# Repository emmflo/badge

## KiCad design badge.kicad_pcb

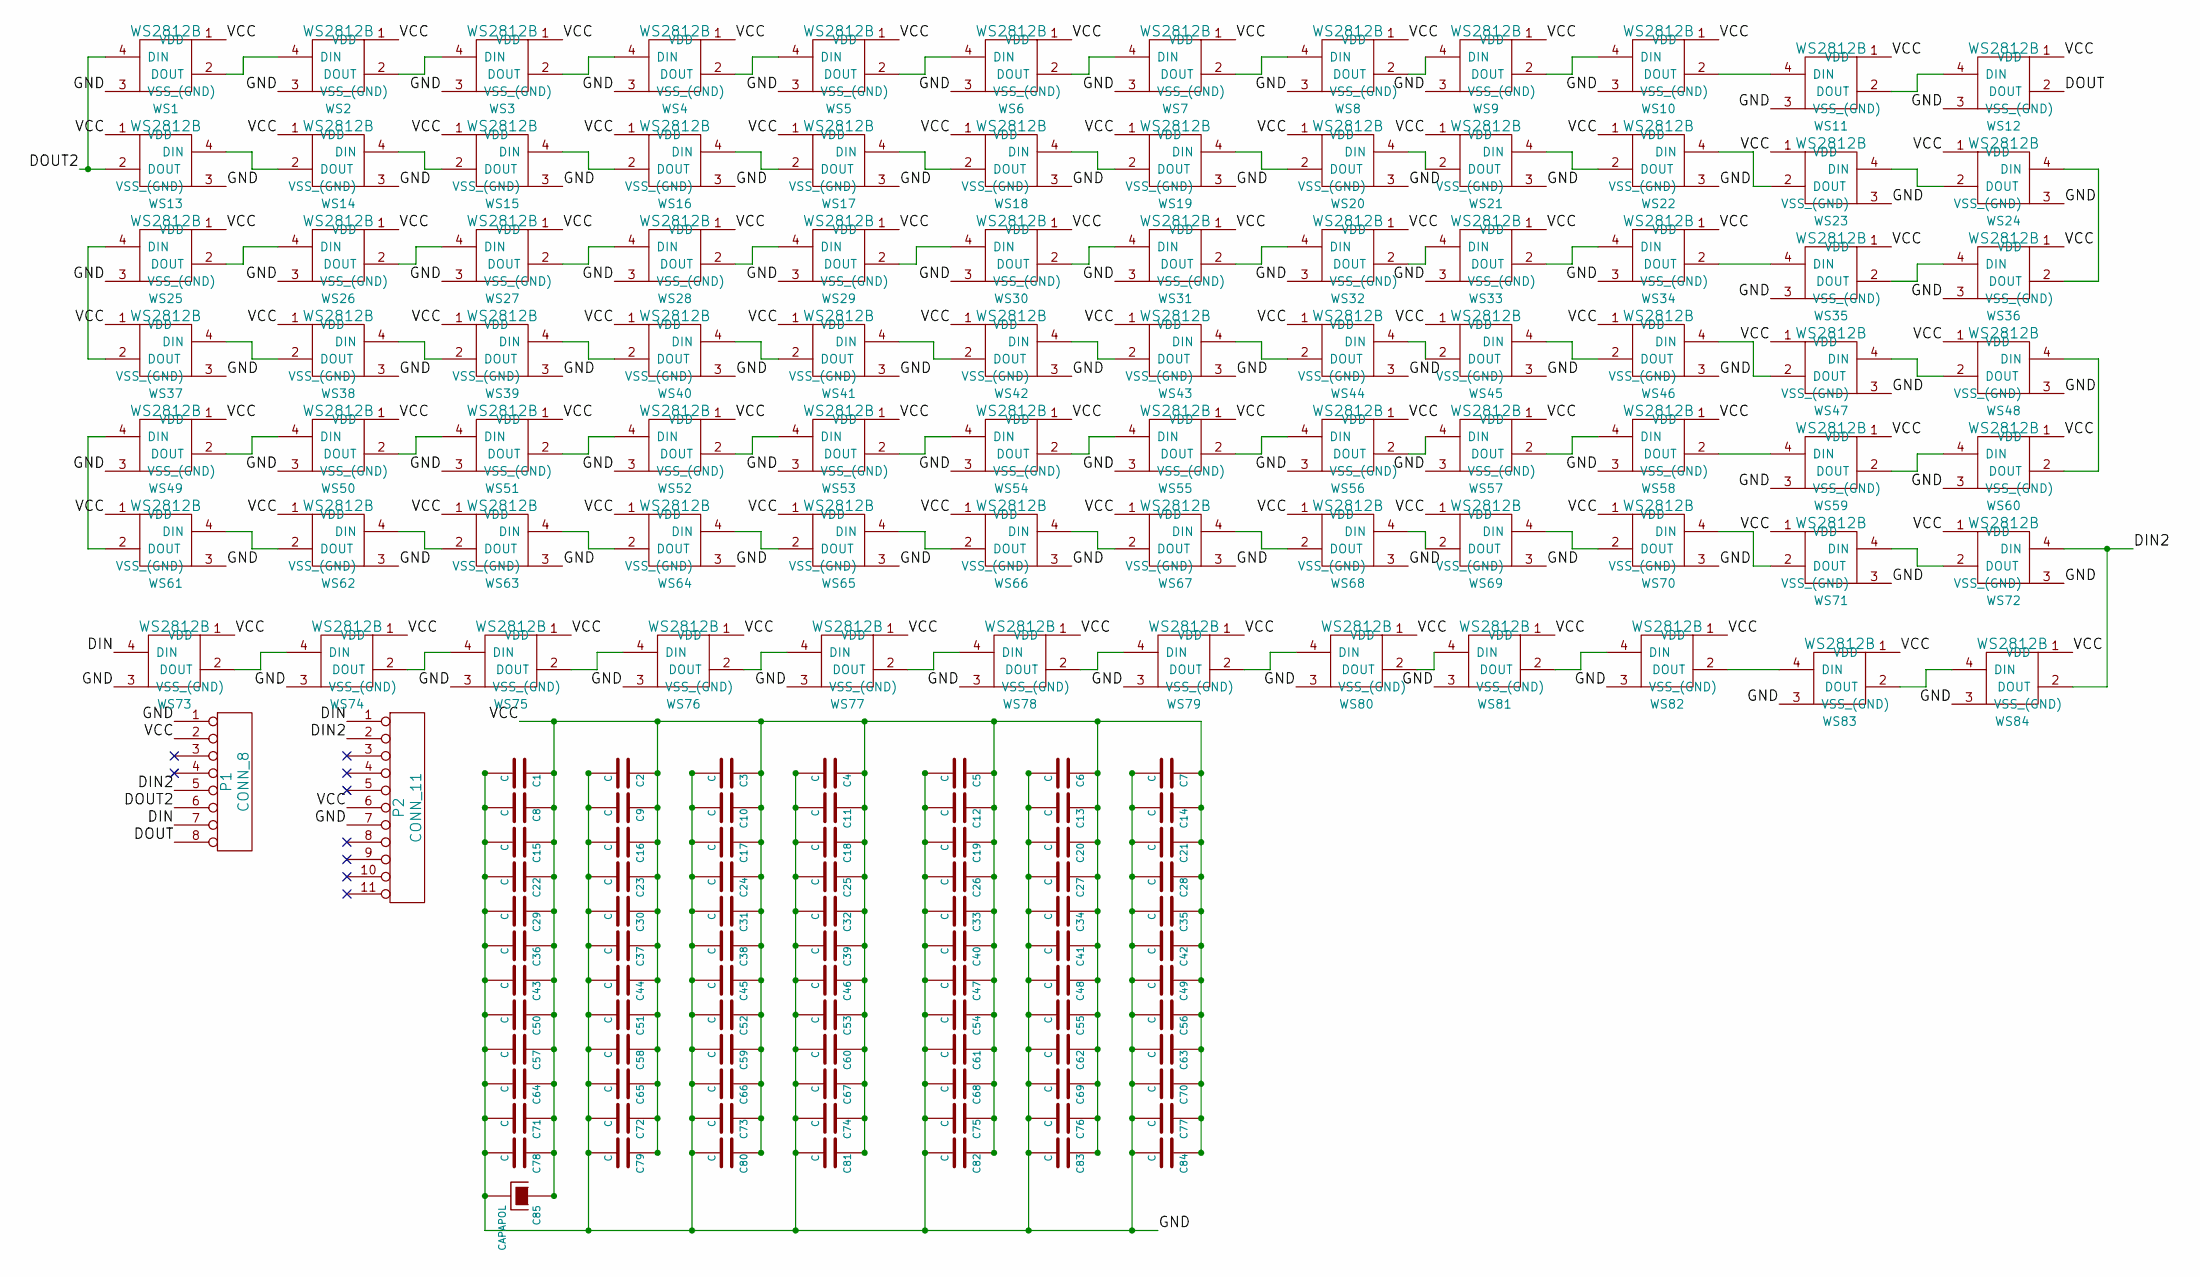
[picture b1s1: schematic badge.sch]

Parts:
C1, C2, C3, C4, C5, C6, C7, C8, C9, C10, C11, C12, C13, C14, C15, C16, C17, C18, C19, C20, C21, C22, C23, C24, C25, C26, C27, C28, C29, C30, C31, C32, C33, C34, C35, C36, C37, C38, C39, C40, C41, C42, C43, C44, C45, C46, C47, C48, C49, C50, C51, C52, C53, C54, C55, C56, C57, C58, C59, C60, C61, C62, C63, C64, C65, C66, C67, C68, C69, C70, C71, C72, C73, C74, C75, C76, C77, C78, C79, C80, C81, C82, C83, C84: C; C_0805_HandSoldering
C85: CAPAPOL
P1: CONN_8; Pin_Header_Straight_1x08
P2: CONN_11
WS1, WS2, WS3, WS4, WS5, WS6, WS7, WS8, WS9, WS10, WS11, WS12, WS13, WS14, WS15, WS16, WS17, WS18, WS19, WS20, WS21, WS22, WS23, WS24, WS25, WS26, WS27, WS28, WS29, WS30, WS31, WS32, WS33, WS34, WS35, WS36, WS37, WS38, WS39, WS40, WS41, WS42, WS43, WS44, WS45, WS46, WS47, WS48, WS49, WS50, WS51, WS52, WS53, WS54, WS55, WS56, WS57, WS58, WS59, WS60, WS61, WS62, WS63, WS64, WS65, WS66, WS67, WS68, WS69, WS70, WS71, WS72, WS73, WS74, WS75, WS76, WS77, WS78, WS79, WS80, WS81, WS82, WS83, WS84: WS2812B

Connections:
/DIN: P1.7, P2.1, WS73.4 (DIN)
/DIN2: P1.5, P2.2, WS72.4 (DIN), WS84.2 (DOUT)
/DOUT: P1.8, WS12.2 (DOUT)
/DOUT2: P1.6, WS1.4 (DIN), WS13.2 (DOUT)
/GND: C1.2, C2.2, C3.2, C4.2, C5.2, C6.2, C7.2, C8.2, C9.2, C10.2, C11.2, C12.2, C13.2, C14.2, C15.2, C16.2, C17.2, C18.2, C19.2, C20.2, C21.2, C22.2, C23.2, C24.2, C25.2, C26.2, C27.2, C28.2, C29.2, C30.2, C31.2, C32.2, C33.2, C34.2, C35.2, C36.2, C37.2, C38.2, C39.2, C40.2, C41.2, C42.2, C43.2, C44.2, C45.2, C46.2, C47.2, C48.2, C49.2, C50.2, C51.2, C52.2, C53.2, C54.2, C55.2, C56.2, C57.2, C58.2, C59.2, C60.2, C61.2, C62.2, C63.2, C64.2, C65.2, C66.2, C67.2, C68.2, C69.2, C70.2, C71.2, C72.2, C73.2, C74.2, C75.2, C76.2, C77.2, C78.2, C79.2, C80.2, C81.2, C82.2, C83.2, C84.2, C85.2, P1.1, P2.7, WS1.3 (VSS_(GND)), WS2.3 (VSS_(GND)), WS3.3 (VSS_(GND)), WS4.3 (VSS_(GND)), WS5.3 (VSS_(GND)), WS6.3 (VSS_(GND)), WS7.3 (VSS_(GND)), WS8.3 (VSS_(GND)), WS9.3 (VSS_(GND)), WS10.3 (VSS_(GND)), WS11.3 (VSS_(GND)), WS12.3 (VSS_(GND)), WS13.3 (VSS_(GND)), WS14.3 (VSS_(GND)), WS15.3 (VSS_(GND)), WS16.3 (VSS_(GND)), WS17.3 (VSS_(GND)), WS18.3 (VSS_(GND)), WS19.3 (VSS_(GND)), WS20.3 (VSS_(GND)), WS21.3 (VSS_(GND)), WS22.3 (VSS_(GND)), WS23.3 (VSS_(GND)), WS24.3 (VSS_(GND)), WS25.3 (VSS_(GND)), WS26.3 (VSS_(GND)), WS27.3 (VSS_(GND)), WS28.3 (VSS_(GND)), WS29.3 (VSS_(GND)), WS30.3 (VSS_(GND)), WS31.3 (VSS_(GND)), WS32.3 (VSS_(GND)), WS33.3 (VSS_(GND)), WS34.3 (VSS_(GND)), WS35.3 (VSS_(GND)), WS36.3 (VSS_(GND)), WS37.3 (VSS_(GND)), WS38.3 (VSS_(GND)), WS39.3 (VSS_(GND)), WS40.3 (VSS_(GND)), WS41.3 (VSS_(GND)), WS42.3 (VSS_(GND)), WS43.3 (VSS_(GND)), WS44.3 (VSS_(GND)), WS45.3 (VSS_(GND)), WS46.3 (VSS_(GND)), WS47.3 (VSS_(GND)), WS48.3 (VSS_(GND)), WS49.3 (VSS_(GND)), WS50.3 (VSS_(GND)), WS51.3 (VSS_(GND)), WS52.3 (VSS_(GND)), WS53.3 (VSS_(GND)), WS54.3 (VSS_(GND)), WS55.3 (VSS_(GND)), WS56.3 (VSS_(GND)), WS57.3 (VSS_(GND)), WS58.3 (VSS_(GND)), WS59.3 (VSS_(GND)), WS60.3 (VSS_(GND)), WS61.3 (VSS_(GND)), WS62.3 (VSS_(GND)), WS63.3 (VSS_(GND)), WS64.3 (VSS_(GND)), WS65.3 (VSS_(GND)), WS66.3 (VSS_(GND)), WS67.3 (VSS_(GND)), WS68.3 (VSS_(GND)), WS69.3 (VSS_(GND)), WS70.3 (VSS_(GND)), WS71.3 (VSS_(GND)), WS72.3 (VSS_(GND)), WS73.3 (VSS_(GND)), WS74.3 (VSS_(GND)), WS75.3 (VSS_(GND)), WS76.3 (VSS_(GND)), WS77.3 (VSS_(GND)), WS78.3 (VSS_(GND)), WS79.3 (VSS_(GND)), WS80.3 (VSS_(GND)), WS81.3 (VSS_(GND)), WS82.3 (VSS_(GND)), WS83.3 (VSS_(GND)), WS84.3 (VSS_(GND))
/VCC: C1.1, C2.1, C3.1, C4.1, C5.1, C6.1, C7.1, C8.1, C9.1, C10.1, C11.1, C12.1, C13.1, C14.1, C15.1, C16.1, C17.1, C18.1, C19.1, C20.1, C21.1, C22.1, C23.1, C24.1, C25.1, C26.1, C27.1, C28.1, C29.1, C30.1, C31.1, C32.1, C33.1, C34.1, C35.1, C36.1, C37.1, C38.1, C39.1, C40.1, C41.1, C42.1, C43.1, C44.1, C45.1, C46.1, C47.1, C48.1, C49.1, C50.1, C51.1, C52.1, C53.1, C54.1, C55.1, C56.1, C57.1, C58.1, C59.1, C60.1, C61.1, C62.1, C63.1, C64.1, C65.1, C66.1, C67.1, C68.1, C69.1, C70.1, C71.1, C72.1, C73.1, C74.1, C75.1, C76.1, C77.1, C78.1, C79.1, C80.1, C81.1, C82.1, C83.1, C84.1, C85.1, P1.2, P2.6, WS1.1 (VDD), WS2.1 (VDD), WS3.1 (VDD), WS4.1 (VDD), WS5.1 (VDD), WS6.1 (VDD), WS7.1 (VDD), WS8.1 (VDD), WS9.1 (VDD), WS10.1 (VDD), WS11.1 (VDD), WS12.1 (VDD), WS13.1 (VDD), WS14.1 (VDD), WS15.1 (VDD), WS16.1 (VDD), WS17.1 (VDD), WS18.1 (VDD), WS19.1 (VDD), WS20.1 (VDD), WS21.1 (VDD), WS22.1 (VDD), WS23.1 (VDD), WS24.1 (VDD), WS25.1 (VDD), WS26.1 (VDD), WS27.1 (VDD), WS28.1 (VDD), WS29.1 (VDD), WS30.1 (VDD), WS31.1 (VDD), WS32.1 (VDD), WS33.1 (VDD), WS34.1 (VDD), WS35.1 (VDD), WS36.1 (VDD), WS37.1 (VDD), WS38.1 (VDD), WS39.1 (VDD), WS40.1 (VDD), WS41.1 (VDD), WS42.1 (VDD), WS43.1 (VDD), WS44.1 (VDD), WS45.1 (VDD), WS46.1 (VDD), WS47.1 (VDD), WS48.1 (VDD), WS49.1 (VDD), WS50.1 (VDD), WS51.1 (VDD), WS52.1 (VDD), WS53.1 (VDD), WS54.1 (VDD), WS55.1 (VDD), WS56.1 (VDD), WS57.1 (VDD), WS58.1 (VDD), WS59.1 (VDD), WS60.1 (VDD), WS61.1 (VDD), WS62.1 (VDD), WS63.1 (VDD), WS64.1 (VDD), WS65.1 (VDD), WS66.1 (VDD), WS67.1 (VDD), WS68.1 (VDD), WS69.1 (VDD), WS70.1 (VDD), WS71.1 (VDD), WS72.1 (VDD), WS73.1 (VDD), WS74.1 (VDD), WS75.1 (VDD), WS76.1 (VDD), WS77.1 (VDD), WS78.1 (VDD), WS79.1 (VDD), WS80.1 (VDD), WS81.1 (VDD), WS82.1 (VDD), WS83.1 (VDD), WS84.1 (VDD)
unnamed: WS1.2 (DOUT), WS2.4 (DIN)
unnamed: WS2.2 (DOUT), WS3.4 (DIN)
unnamed: WS3.2 (DOUT), WS4.4 (DIN)
unnamed: WS4.2 (DOUT), WS5.4 (DIN)
unnamed: WS5.2 (DOUT), WS6.4 (DIN)
unnamed: WS6.2 (DOUT), WS7.4 (DIN)
unnamed: WS7.2 (DOUT), WS8.4 (DIN)
unnamed: WS8.2 (DOUT), WS9.4 (DIN)
unnamed: WS10.2 (DOUT), WS11.4 (DIN)
unnamed: WS9.2 (DOUT), WS10.4 (DIN)
unnamed: WS11.2 (DOUT), WS12.4 (DIN)
unnamed: WS13.4 (DIN), WS14.2 (DOUT)
unnamed: WS14.4 (DIN), WS15.2 (DOUT)
unnamed: WS15.4 (DIN), WS16.2 (DOUT)
unnamed: WS16.4 (DIN), WS17.2 (DOUT)
unnamed: WS17.4 (DIN), WS18.2 (DOUT)
unnamed: WS18.4 (DIN), WS19.2 (DOUT)
unnamed: WS19.4 (DIN), WS20.2 (DOUT)
unnamed: WS20.4 (DIN), WS21.2 (DOUT)
unnamed: WS21.4 (DIN), WS22.2 (DOUT)
unnamed: WS22.4 (DIN), WS23.2 (DOUT)
unnamed: WS23.4 (DIN), WS24.2 (DOUT)
unnamed: WS24.4 (DIN), WS36.2 (DOUT)
unnamed: WS25.2 (DOUT), WS26.4 (DIN)
unnamed: WS25.4 (DIN), WS37.2 (DOUT)
unnamed: WS26.2 (DOUT), WS27.4 (DIN)
unnamed: WS27.2 (DOUT), WS28.4 (DIN)
unnamed: WS28.2 (DOUT), WS29.4 (DIN)
unnamed: WS29.2 (DOUT), WS30.4 (DIN)
unnamed: WS30.2 (DOUT), WS31.4 (DIN)
unnamed: WS31.2 (DOUT), WS32.4 (DIN)
unnamed: WS32.2 (DOUT), WS33.4 (DIN)
unnamed: WS33.2 (DOUT), WS34.4 (DIN)
unnamed: WS34.2 (DOUT), WS35.4 (DIN)
unnamed: WS35.2 (DOUT), WS36.4 (DIN)
unnamed: WS37.4 (DIN), WS38.2 (DOUT)
unnamed: WS38.4 (DIN), WS39.2 (DOUT)
unnamed: WS39.4 (DIN), WS40.2 (DOUT)
unnamed: WS40.4 (DIN), WS41.2 (DOUT)
unnamed: WS41.4 (DIN), WS42.2 (DOUT)
unnamed: WS42.4 (DIN), WS43.2 (DOUT)
unnamed: WS43.4 (DIN), WS44.2 (DOUT)
unnamed: WS44.4 (DIN), WS45.2 (DOUT)
unnamed: WS45.4 (DIN), WS46.2 (DOUT)
unnamed: WS46.4 (DIN), WS47.2 (DOUT)
unnamed: WS47.4 (DIN), WS48.2 (DOUT)
unnamed: WS48.4 (DIN), WS60.2 (DOUT)
unnamed: WS49.2 (DOUT), WS50.4 (DIN)
unnamed: WS49.4 (DIN), WS61.2 (DOUT)
unnamed: WS50.2 (DOUT), WS51.4 (DIN)
unnamed: WS51.2 (DOUT), WS52.4 (DIN)
unnamed: WS52.2 (DOUT), WS53.4 (DIN)
unnamed: WS53.2 (DOUT), WS54.4 (DIN)
unnamed: WS54.2 (DOUT), WS55.4 (DIN)
unnamed: WS55.2 (DOUT), WS56.4 (DIN)
unnamed: WS56.2 (DOUT), WS57.4 (DIN)
unnamed: WS57.2 (DOUT), WS58.4 (DIN)
unnamed: WS58.2 (DOUT), WS59.4 (DIN)
unnamed: WS59.2 (DOUT), WS60.4 (DIN)
unnamed: WS61.4 (DIN), WS62.2 (DOUT)
unnamed: WS62.4 (DIN), WS63.2 (DOUT)
unnamed: WS63.4 (DIN), WS64.2 (DOUT)
unnamed: WS64.4 (DIN), WS65.2 (DOUT)
unnamed: WS65.4 (DIN), WS66.2 (DOUT)
unnamed: WS66.4 (DIN), WS67.2 (DOUT)
unnamed: WS67.4 (DIN), WS68.2 (DOUT)
unnamed: WS68.4 (DIN), WS69.2 (DOUT)
unnamed: WS69.4 (DIN), WS70.2 (DOUT)
unnamed: WS70.4 (DIN), WS71.2 (DOUT)
unnamed: WS71.4 (DIN), WS72.2 (DOUT)
unnamed: WS73.2 (DOUT), WS74.4 (DIN)
unnamed: WS74.2 (DOUT), WS75.4 (DIN)
unnamed: WS75.2 (DOUT), WS76.4 (DIN)
unnamed: WS76.2 (DOUT), WS77.4 (DIN)
unnamed: WS77.2 (DOUT), WS78.4 (DIN)
unnamed: WS78.2 (DOUT), WS79.4 (DIN)
unnamed: WS79.2 (DOUT), WS80.4 (DIN)
unnamed: WS80.2 (DOUT), WS81.4 (DIN)
unnamed: WS81.2 (DOUT), WS82.4 (DIN)
unnamed: WS82.2 (DOUT), WS83.4 (DIN)
unnamed: WS83.2 (DOUT), WS84.4 (DIN)

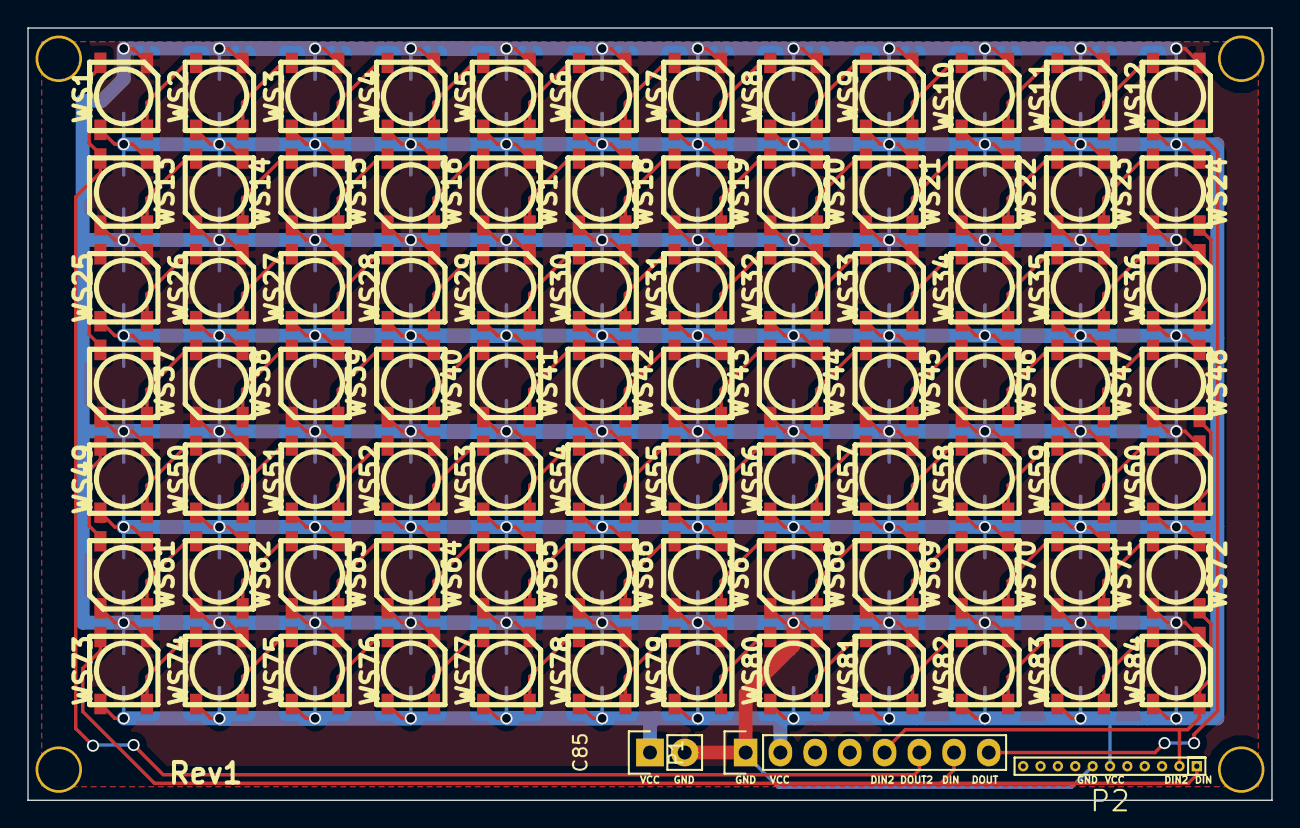
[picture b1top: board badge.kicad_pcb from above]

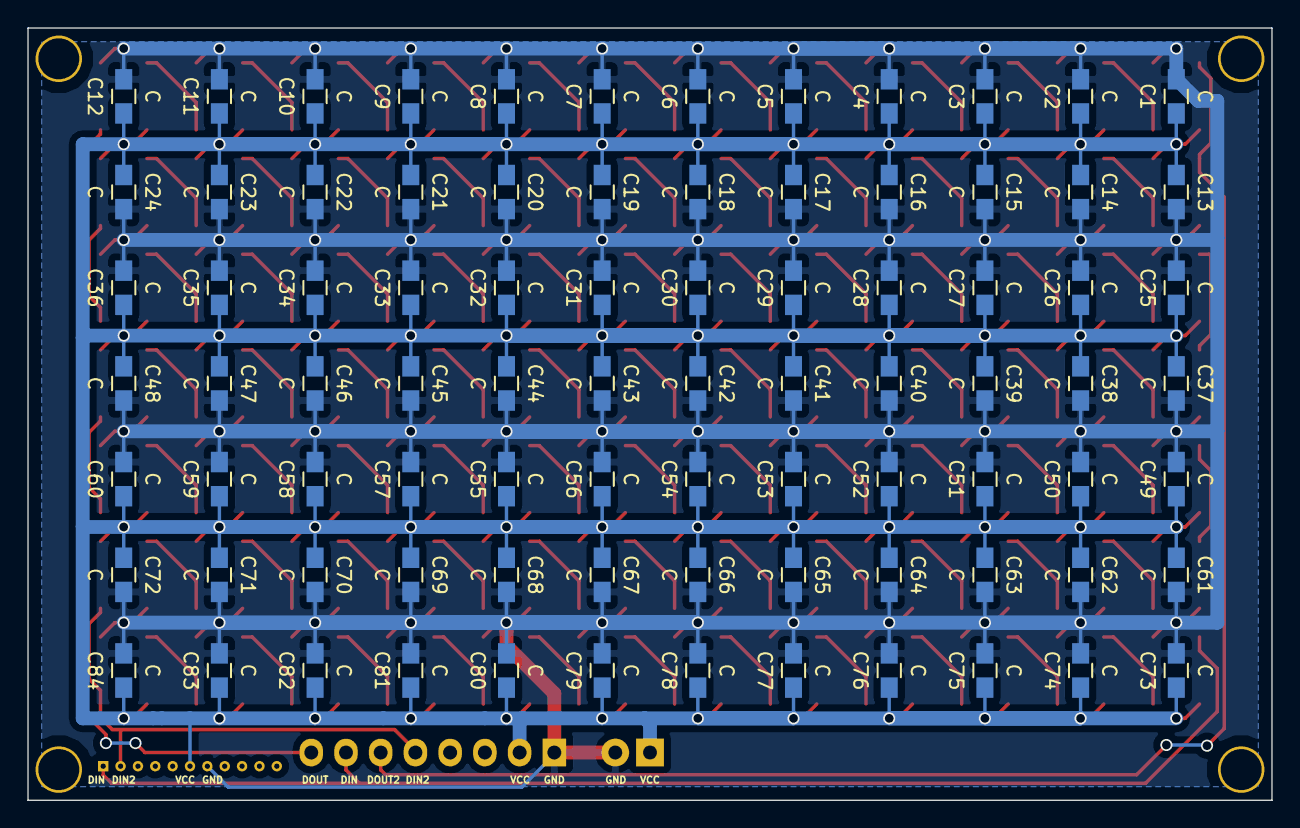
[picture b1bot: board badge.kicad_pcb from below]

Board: 2 copper layers, 91.0 x 56.5 mm, 171 parts (84 on the bottom side), 87 nets.

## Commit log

2015-03-01 First commit.
2015-03-01 sch was broken, corrected
2015-03-01 Addition of second data input so we can unpopulate first and last row.
2015-03-05 Rev1 Added ground plan and mounting holes. Put some labels on silkscreen.
2015-03-05 First seeedstudio test
2015-04-29 Add code
2015-04-29 template-code
2015-05-28 Avancement sur le code pour atmega328
2015-05-31 It works ! :>
2015-06-01 Font
2015-06-02 Text !
2015-06-02 ASCII_Extended. IRC bot working :P
2015-06-04 Tests on SD card (well my setup is working but for the first prototype I think I'll drop SD card support because the lack of space)
2015-06-04 Changed pyglet test to match last firmware
